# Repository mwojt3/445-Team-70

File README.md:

# 445-Team-70
Markdown lab notebook for team 70's project: automatic drum tuner

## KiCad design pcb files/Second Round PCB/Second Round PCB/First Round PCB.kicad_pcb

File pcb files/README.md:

this is where we shall place all of our printed circuit pcb board files

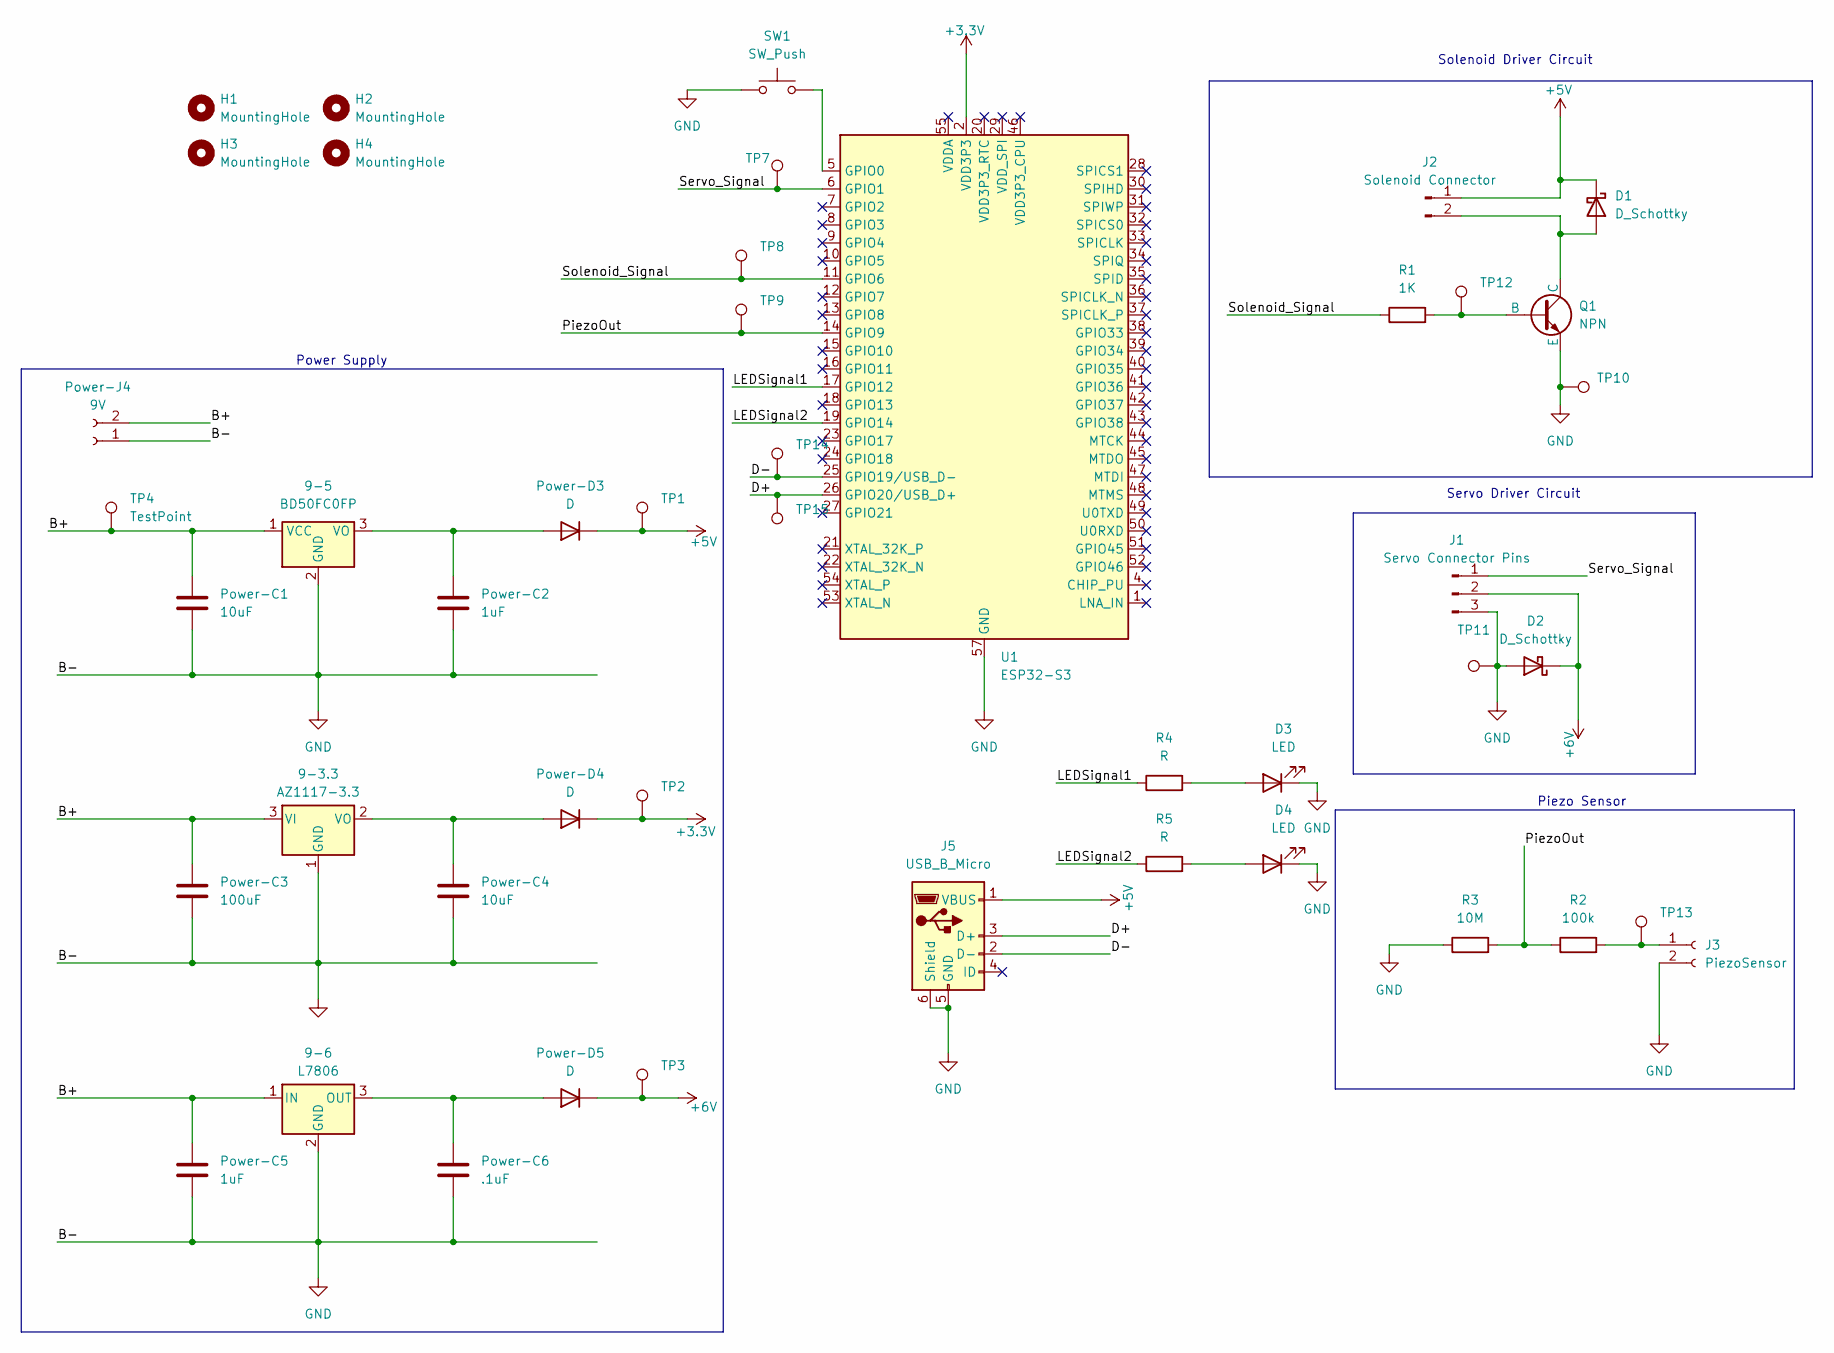
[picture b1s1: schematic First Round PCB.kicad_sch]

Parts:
9-3.3: AZ1117-3.3; TO-252-3_TabPin2
9-5: BD50FC0FP; TO-252-2
9-6: L7806; TO-263-3_TabPin2
D1, D2: D_Schottky; D_SMA-SMB_Universal_Handsoldering
D3, D4: LED; LED_D3.0mm
H1, H2, H3, H4: MountingHole; MountingHole_3.2mm_M3
J1: Servo Connector Pins; Molex_KK-254_AE-6410-03A_1x03_P2.54mm_Vertical
J2: Solenoid Connector; Molex_KK-254_AE-6410-02A_1x02_P2.54mm_Vertical
J3: PiezoSensor; Molex_KK-254_AE-6410-02A_1x02_P2.54mm_Vertical
J5: USB_B_Micro; USB_Micro-B_Amphenol_10118194-0001LF_Horizontal
Power-C1, Power-C4: 10uF; C_0805_2012Metric_Pad1.18x1.45mm_HandSolder
Power-C2, Power-C5: 1uF; C_0805_2012Metric_Pad1.18x1.45mm_HandSolder
Power-C3: 100uF; C_0805_2012Metric_Pad1.18x1.45mm_HandSolder
Power-C6: .1uF; C_0805_2012Metric_Pad1.18x1.45mm_HandSolder
Power-D3, Power-D4, Power-D5: D; D_SMA-SMB_Universal_Handsoldering
Power-J4: 9V; Molex_KK-254_AE-6410-02A_1x02_P2.54mm_Vertical
Q1: NPN; TO-262-3_Vertical
R1: 1K; R_0805_2012Metric_Pad1.20x1.40mm_HandSolder
R2: 100k; R_0805_2012Metric_Pad1.20x1.40mm_HandSolder
R3: 10M; R_0805_2012Metric_Pad1.20x1.40mm_HandSolder
R4, R5: R; R_0805_2012Metric_Pad1.20x1.40mm_HandSolder
SW1: SW_Push; SW_SPST_PTS647_Sx38
TP1, TP2, TP3, TP4, TP7, TP8, TP9, TP10, TP11, TP12, TP13, TP14, TP15: TestPoint; TestPoint_Pad_D2.0mm
U1: ESP32-S3; QFN-56-1EP_7x7mm_P0.4mm_EP4x4mm

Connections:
+3.3V: Power-D4.1 (K), TP2.1, U1.2 (VDD3P3), U1.3 (VDD3P3)
+5V: D1.1 (K), J2.1, J5.1 (VBUS), Power-D3.1 (K), TP1.1
+6V: D2.1 (K), J1.2, Power-D5.1 (K), TP3.1
/B+: 9-3.3.3 (VI), 9-5.1 (VCC), 9-6.1 (IN), Power-C1.1, Power-C3.1, Power-C5.1, Power-J4.2, TP4.1; also elsewhere on the board
/D+: J5.3 (D+), TP15.1, U1.26 (GPIO20/USB_D+)
/D-: J5.2 (D-), TP14.1, U1.25 (GPIO19/USB_D-)
/LEDSignal1: R4.1, U1.17 (GPIO12)
/LEDSignal2: R5.1, U1.19 (GPIO14)
/PiezoOut: R2.1, R3.2, TP9.1, U1.14 (GPIO9)
/Servo_Signal: J1.1, TP7.1, U1.6 (GPIO1)
/Solenoid_Signal: R1.1, TP8.1, U1.11 (GPIO6)
GND: 9-3.3.1 (GND), 9-5.2 (GND), 9-6.2 (GND), D2.2 (A), D3.1 (K), D4.1 (K), J1.3, J3.2, J5.5 (GND), J5.6 (Shield), Power-C1.2, Power-C2.2, Power-C3.2, Power-C4.2, Power-C5.2, Power-C6.2, Power-J4.1, Q1.3 (E), R3.1, SW1.1, TP10.1, TP11.1, U1.57 (GND)
unnamed: 9-3.3.2 (VO), Power-C4.1, Power-D4.2 (A)
unnamed: 9-5.3 (VO), Power-C2.1, Power-D3.2 (A)
unnamed: 9-6.3 (OUT), Power-C6.1, Power-D5.2 (A)
unnamed: D1.2 (A), J2.2, Q1.1 (C)
unnamed: D3.2 (A), R4.2
unnamed: D4.2 (A), R5.2
unnamed: J3.1, R2.2, TP13.1
unnamed: Q1.2 (B), R1.2, TP12.1
unnamed: SW1.2, U1.5 (GPIO0)

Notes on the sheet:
Solenoid Driver Circuit
Power Supply
Servo Driver Circuit
Piezo Sensor

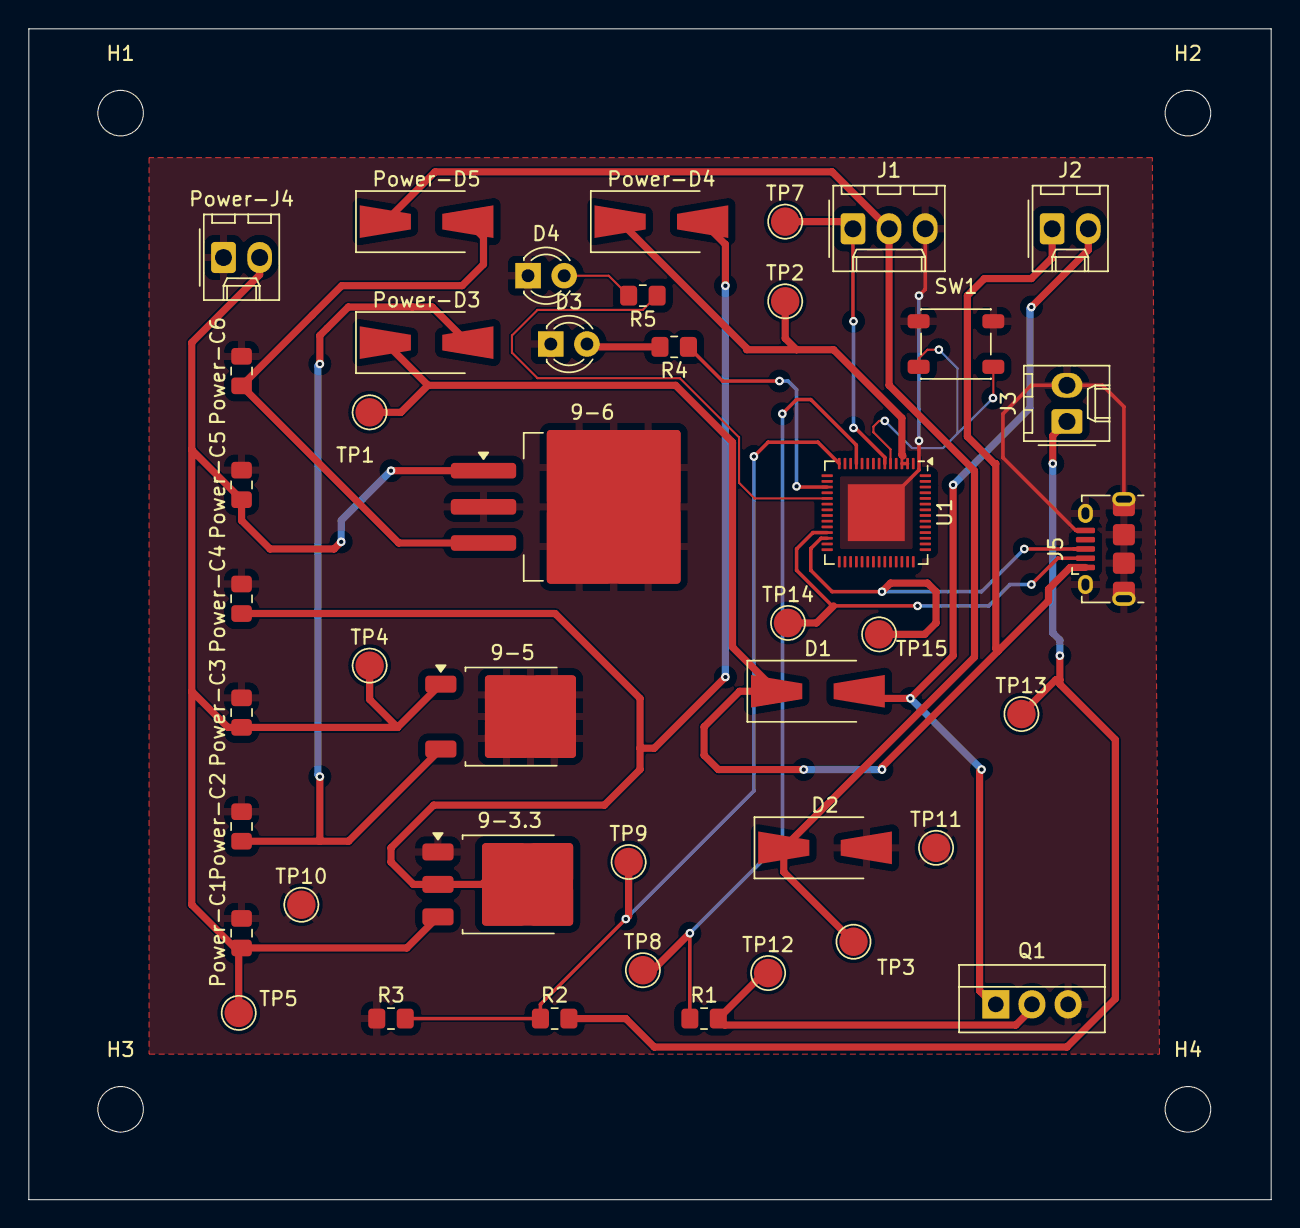
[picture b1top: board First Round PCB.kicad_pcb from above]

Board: 2 copper layers, 87.3 x 82.3 mm, 47 parts (0 on the bottom side), 21 nets.

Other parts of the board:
TP5: TestPoint; TestPoint_Pad_D2.0mm

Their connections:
/B+: TP5.1; also elsewhere on the board

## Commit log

2025-02-14 Create README.md for pcb and folder for pcb files
2025-02-14 added place for our code
2025-02-14 models folder
2025-02-28 First Version of PCB
2025-02-28 First Round PCB
2025-05-08 Adding servo adapter CAD and stl files
2025-05-08 Create STM prototyping folder
2025-05-08 Added STM prototype
2025-05-08 Microphone testing in ArduinoIDE
